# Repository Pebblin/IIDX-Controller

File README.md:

# IIDX-Controller

Repo for the funny:tm: summer project

Will throw more stuff here eventually surely

I have decided to make the PCBs usable for SDVX as well (has two inputs for encoders) 

## TOOD:

Items below subject to change

| Item | Start Date | Completion Date | Notes |
| --- | :---: | :---: | --- |
| ~~Create GitHub Repo~~ | `5/29/2026` | `5/29/2026` | This should've been done first oops |
| Create Assembly BOM | `5/28/2026` | | Button Set Added |
| ~~Create Breakout Board BOM~~ | `6/4/2026` | `6/10/2026` | Done |
| Create MCU Board BOM | `5/28/2026` | | Missing Driver + Connectors |
| EDA: PCB Schematic | `5/28/2026` | | Breakout Done |
| EDA: PCB Layout | `6/7/2026` | | Breakout Done |
| CAD: Turntable | | | |
| CAD: Panel Buttons | | | |
| CAD: Case | | | |
| CAD: Internals | | | |
| CAD: Create Assembly/Model | | | |
| Program MCU Logic | | | |
| Acquire Parts | | | |
| Solder PCB | | | |
| Assemble Controller | | | |

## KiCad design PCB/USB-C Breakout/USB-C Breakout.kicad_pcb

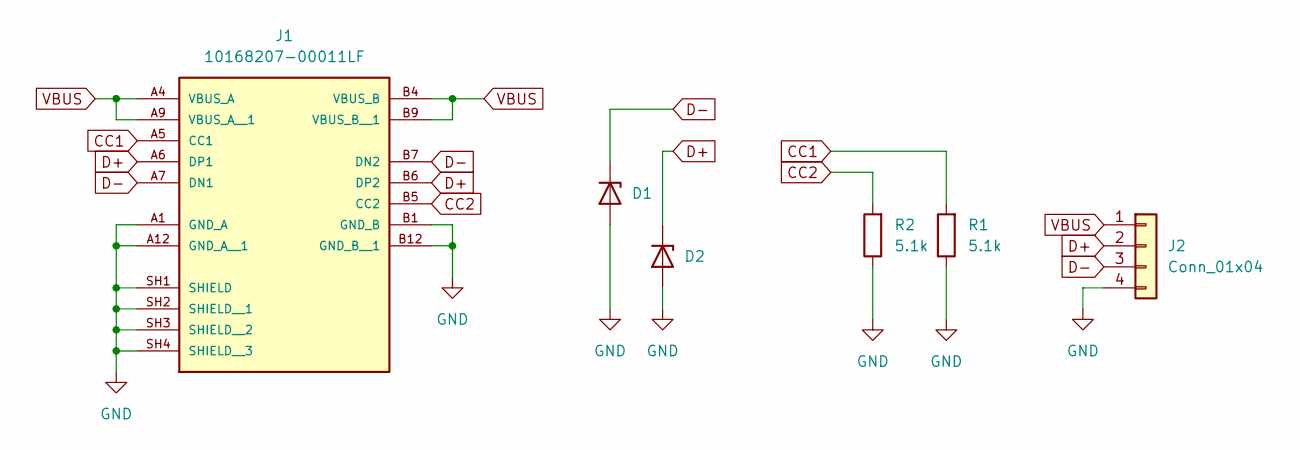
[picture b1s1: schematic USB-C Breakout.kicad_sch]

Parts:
D1, D2: ESD321DYAR; SOT5x3_DYA_TEX
J1: 10168207-00011LF; USB-C-TH_SHOUHAN_TYPE-C-14PLC-H10.0; PARTREV A
J2: Conn_01x04; JST_XH_B4B-XH-AM_1x04_P2.50mm_Vertical
R1, R2: 5.1k; RESC1608X55N

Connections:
CC1: J1.A5 (CC1), R1.2
CC2: J1.B5 (CC2), R2.2
D+: D2.1 (K), J1.A6 (DP1), J1.B6 (DP2), J2.2
D-: D1.1 (K), J1.A7 (DN1), J1.B7 (DN2), J2.3
GND: D1.2 (A), D2.2 (A), J1.A1 (GND_A), J1.A12 (GND_A__1), J1.B1 (GND_B), J1.B12 (GND_B__1), J1.SH1 (SHIELD), J1.SH2 (SHIELD__1), J1.SH3 (SHIELD__2), J1.SH4 (SHIELD__3), J2.4, R1.1, R2.1
VBUS: J1.A4 (VBUS_A), J1.A9 (VBUS_A__1), J1.B4 (VBUS_B), J1.B9 (VBUS_B__1), J2.1

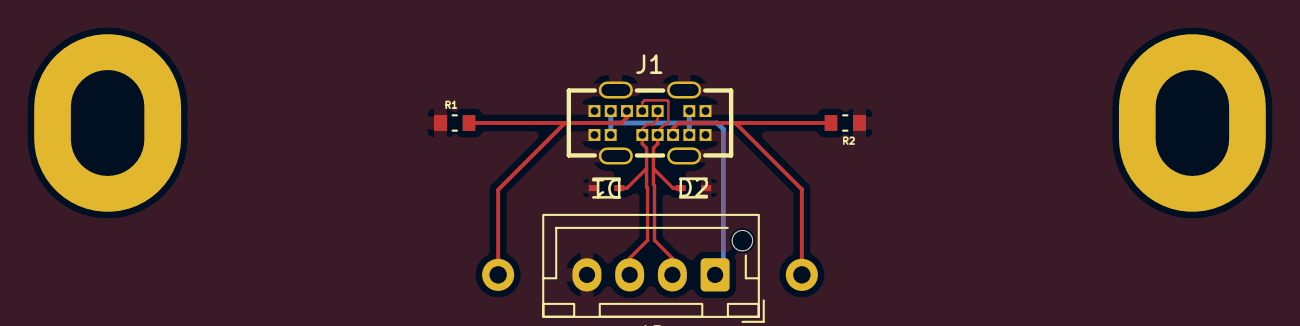
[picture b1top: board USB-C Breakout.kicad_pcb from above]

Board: 2 copper layers, 6 parts (0 on the bottom side), 6 nets.

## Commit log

2026-05-30 Repo init
2026-05-30 Added EDA files
2026-06-11 Renamed stuff and finished breakout board
2026-06-12 MCU Library
2026-06-12 Most of MCU schematic done
2026-06-16 Final Schematic Touches
2026-06-21 A few more breakout board changes (need to fix rest of issues in the DRC)
